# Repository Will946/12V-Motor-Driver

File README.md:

# TB6612FNG Motor Driver Board

A single-IC dual-channel DC motor driver board built around the Toshiba **TB6612FNG**. It accepts a 12V motor supply and 3.3V logic supply, and drives two motors (or other DC loads) via direct GPIO control — no PWM enable line or standby control required.

## Board Render

## Schematic

## Overview

This board breaks out one TB6612FNG dual H-bridge driver IC with all required support circuitry: power decoupling, a power-good LED indicator, and header connectors for power, control signals, and motor outputs. It's designed to be one repeatable "cell" in a multi-board or multi-instance motor control system. Multiple copies of this board can be powered from a shared 12V/3.3V/GND distribution and controlled independently from a microcontroller.

## What It's For

Driving small DC motors (e.g. brushed DC motors, peristaltic pump motors, gear motors) that:
- Run on 12V
- Draw up to ~1.2A continuous / 3.2A peak per channel
- Only need simple on/off or forward/reverse control (no onboard speed ramping required, though PWM control is possible if rewired)

Each board drives **two independent motors** (Channel A and Channel B).

## Key Design Decisions

- **STBY tied directly to VCC** — the IC is always active, no software standby control. Simplifies control to just the IN1/IN2 pins.
- **PWMA and PWMB tied directly to VCC** — both channels run at full enable at all times. Motor on/off and direction are controlled purely through AIN1/AIN2 and BIN1/BIN2 logic levels, not PWM gating.
- **No GPIO required for STBY/PWMA/PWMB** — frees up microcontroller pins; only 4 GPIOs are needed per board (2 per channel).
- **Multiple parallel pins for VM and GND** at the board connectors — spreads motor current across multiple contacts to reduce resistance and heat at the interconnect.
- **Single pin for VCC** — logic current draw is negligible (a few mA), so no need for parallel contacts.

## Bill of Materials (Key Components)

| Ref | Part | Function |
|-----|------|----------|
| U1 | TB6612FNG (SSOP-24) | Dual H-bridge motor driver IC |
| C6 | 0.1 µF ceramic | High-frequency decoupling, VM rail (placed close to IC) |
| C7 | 10 µF | Bulk decoupling, VM rail |
| C8 | 0.1 µF ceramic | High-frequency decoupling, VCC rail (placed close to IC) |
| C9 | 10 µF | Bulk decoupling, VCC rail |
| R2 | 2.4 kΩ | Current-limiting resistor for power indicator LED (fed from VM) |
| D2 | LED | Power-on indicator, lit whenever VM is present |
| J1 | 5-pin socket | Motor output connector (AO1, AO2, BO1, BO2 + GND) |
| J2 | 5-pin socket | Control input connector (AIN1, AIN2, BIN1, BIN2 + GND) |
| J3 | 5-pin socket | VM power input connector (VM ×3, GND ×1 — parallel pins for current capacity) |
| J6 | 3-pin socket | VCC logic power connector (VCC ×2, GND ×1) |

## Pinout / Connector Reference

### J1 — Motor Outputs
| Pin | Net |
|-----|-----|
| 1 | BO1 |
| 2 | BO2 |
| 3 | GND |
| 4 | AO2 |
| 5 | AO1 |

### J2 — Control Inputs (from microcontroller)
| Pin | Net |
|-----|-----|
| 1 | AIN2 |
| 2 | AIN1 |
| 3 | GND |
| 4 | BIN1 |
| 5 | BIN2 |

### J3 — Motor Power Input (12V)
| Pin | Net |
|-----|-----|
| 1 | VM |
| 2 | VM |
| 3 | GND |
| 4 | VM |
| 5 | VM |

### J6 — Logic Power Input (3.3V)
| Pin | Net |
|-----|-----|
| 1 | VCC |
| 2 | VCC |
| 3 | GND |

## Operation

### Power-up
1. Connect 12V to J3 (VM) and 3.3V to J6 (VCC). Both share GND with the rest of the system.
2. The power indicator LED (D2) lights immediately whenever VM is present, confirming motor supply is live.
3. Because STBY, PWMA, and PWMB are hardwired to VCC, the IC is fully active as soon as VCC is applied — no initialization sequence or enable command is needed.

### Motor Control Logic

Each channel (A and B) is controlled by a pair of logic inputs:

| IN1 | IN2 | Output State |
|-----|-----|--------------|
| H | L | Motor runs forward |
| L | H | Motor runs reverse |
| L | L | Motor stopped (outputs low, coasting) |
| H | H | Short brake |

For simple on/off (single-direction) loads, tie the unused direction input low and drive only one input HIGH/LOW from the microcontroller to start/stop the motor.

### Control Pin Summary
- **AIN1 / AIN2** → Channel A direction/on-off control (from MCU GPIO)
- **BIN1 / BIN2** → Channel B direction/on-off control (from MCU GPIO)
- **STBY, PWMA, PWMB** → hardwired to VCC on this board, not exposed for external control

## Power Requirements

- **VM (Motor Supply):** 4.5V–13.5V, sized for 12V operation. Up to ~1.2A continuous / 3.2A peak per channel (2.4A/6.4A total for both channels, observing thermal limits).
- **VCC (Logic Supply):** 2.7V–5.5V, 3.3V intended. Draws only a few mA — no special supply requirements.
- **GND:** Common return for both VM and VCC. Shared across all connectors.

## Design Notes

- **Decoupling placement:** The 0.1 µF ceramic caps on both VM and VCC are placed as close as possible to the IC's power pins to suppress high-frequency switching noise. The 10 µF bulk caps support transient current demand during motor start and provide additional local energy storage.
- **Multiple VM/PGND IC pins** (VM1/VM2/VM3 and PGND1/PGND2) are all tied together on the PCB — this is standard practice for this package, distributing current across more pads to reduce localized resistance and heating.
- **Connector current sharing:** J3 (VM) and the GND return use multiple parallel pins specifically to handle motor current without overloading a single contact. J2 (control signals) and J6 (VCC) use single pins per net since signal/logic current is negligible.
- **No exposed thermal pad:** The SSOP-24 package has no bottom thermal pad, so copper traces may be routed underneath the IC footprint without conflict.

## Intended Use in a Larger System

This board is designed as a repeatable unit, multiple instances can be deployed in parallel, each independently controlled via its own J2 connector, while sharing a common 12V and 3.3V distribution through J3/J6. This allows a single microcontroller to drive many motor channels (4 GPIOs per board) without needing per-board enable/standby management.

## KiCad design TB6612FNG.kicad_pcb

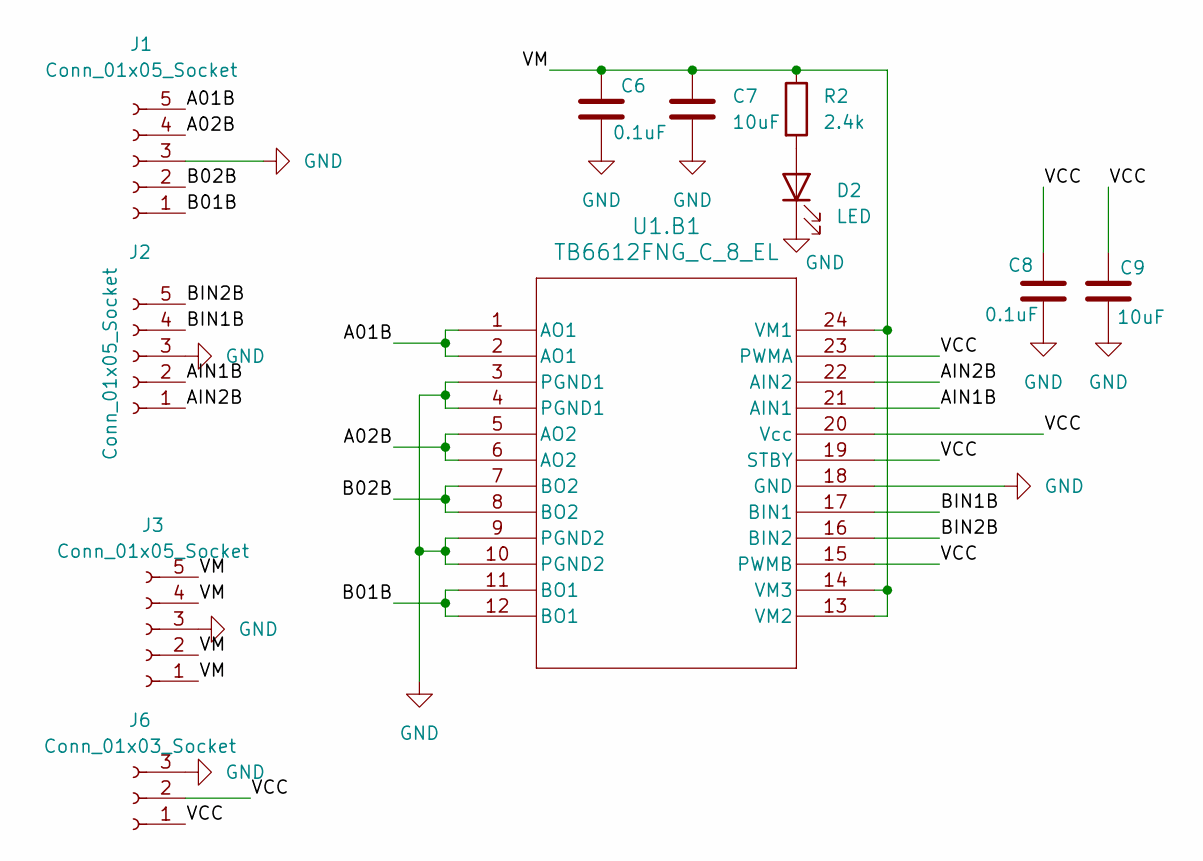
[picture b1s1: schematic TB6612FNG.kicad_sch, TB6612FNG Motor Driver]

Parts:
C6, C8: 0.1uF; C_0805_2012Metric_Pad1.18x1.45mm_HandSolder
C7, C9: 10uF; C_0805_2012Metric_Pad1.18x1.45mm_HandSolder
D2: LED; LED_0805_2012Metric_Pad1.15x1.40mm_HandSolder
J1, J2, J3: Conn_01x05_Socket; PinHeader_1x05_P2.54mm_Vertical
J6: Conn_01x03_Socket; PinHeader_1x03_P2.54mm_Vertical
R2: 2.4k; R_0805_2012Metric_Pad1.20x1.40mm_HandSolder
U1.B1: TB6612FNG_C_8_EL; TB6612FNG

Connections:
/A01B: J1.5, U1.B1.1 (AO1), U1.B1.2 (AO1)
/A02B: J1.4, U1.B1.5 (AO2), U1.B1.6 (AO2)
/AIN1B: J2.2, U1.B1.21 (AIN1)
/AIN2B: J2.1, U1.B1.22 (AIN2)
/B01B: J1.1, U1.B1.11 (BO1), U1.B1.12 (BO1)
/B02B: J1.2, U1.B1.7 (BO2), U1.B1.8 (BO2)
/BIN1B: J2.4, U1.B1.17 (BIN1)
/BIN2B: J2.5, U1.B1.16 (BIN2)
/VCC: C8.1, C9.1, J6.1, J6.2, U1.B1.15 (PWMB), U1.B1.19 (STBY), U1.B1.20 (Vcc), U1.B1.23 (PWMA)
/VM: C6.1, C7.1, J3.1, J3.2, J3.4, J3.5, R2.1, U1.B1.13 (VM2), U1.B1.14 (VM3), U1.B1.24 (VM1)
GND: C6.2, C7.2, C8.2, C9.2, D2.1 (K), J1.3, J2.3, J3.3, J6.3, U1.B1.3 (PGND1), U1.B1.4 (PGND1), U1.B1.9 (PGND2), U1.B1.10 (PGND2), U1.B1.18 (GND)
unnamed: D2.2 (A), R2.2

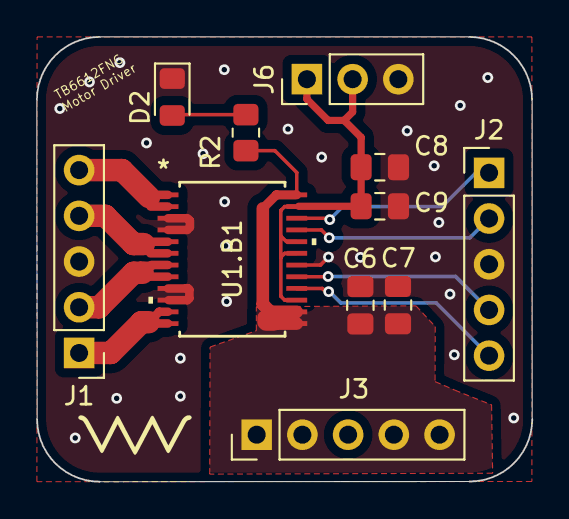
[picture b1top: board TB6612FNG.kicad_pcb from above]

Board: 2 copper layers, 27.5 x 24.7 mm, 11 parts (0 on the bottom side), 12 nets.

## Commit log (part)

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2026-06-20 Rename README (1).md to README.md
